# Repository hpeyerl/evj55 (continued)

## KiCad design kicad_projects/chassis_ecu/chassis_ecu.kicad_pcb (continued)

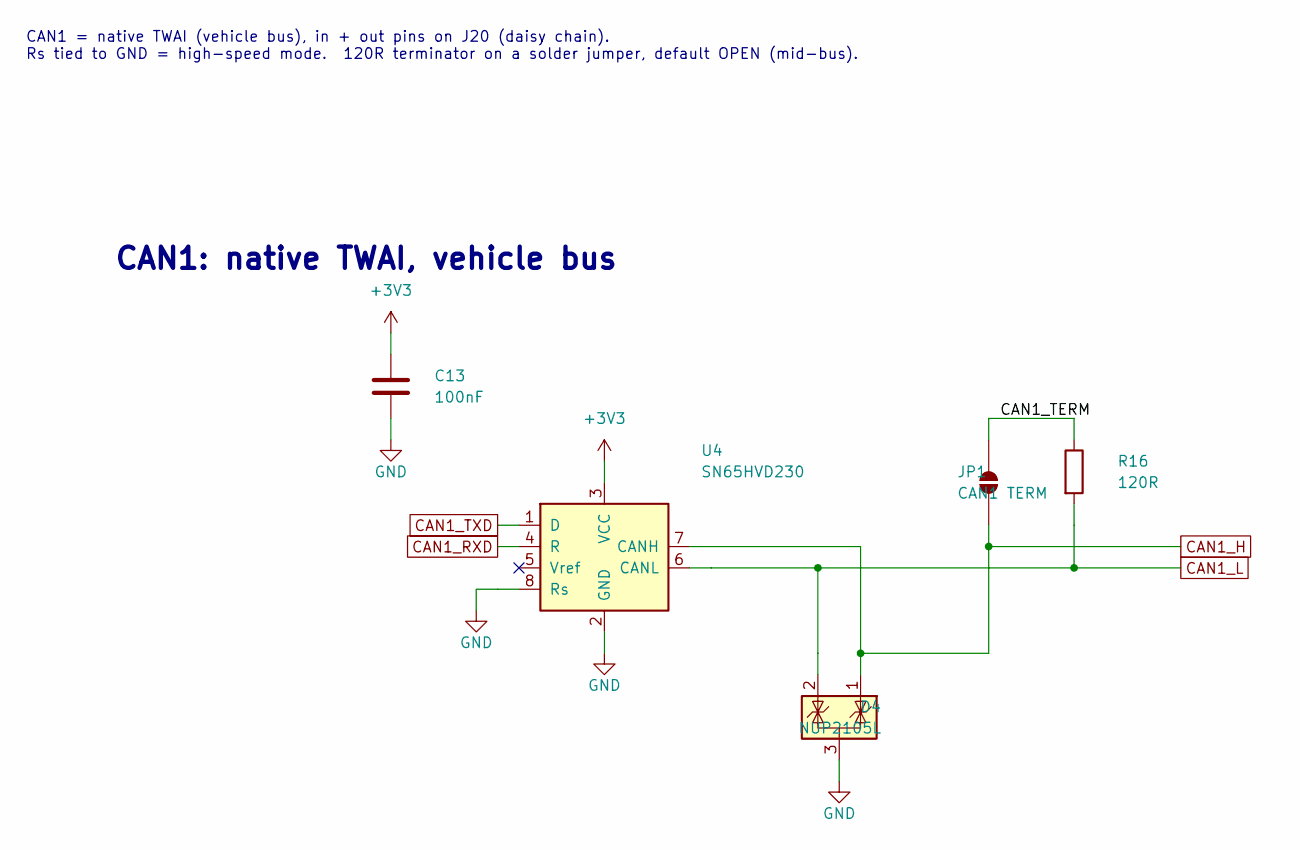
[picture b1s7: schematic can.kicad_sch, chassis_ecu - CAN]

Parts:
C13: 100nF; C_0603_1608Metric; MPN CC0603KRX7R9BB104; LCSC C14663
D4: NUP2105L; SOT-23; MPN NUP2105LT1G; LCSC C14486
JP1: CAN1 TERM; SolderJumper-2_P1.3mm_Open_RoundedPad1.0x1.5mm
R16: 120R; R_1206_3216Metric; MPN 1206W4F1200T5E; LCSC C17909
U4: SN65HVD230; SOIC-8_3.9x4.9mm_P1.27mm; MPN SN65HVD230DR; LCSC C12084

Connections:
+3V3: C13.1, U4.3 (VCC); also elsewhere on the board
/CAN/CAN1_TERM: JP1.2 (B), R16.1
CAN1_H: D4.1 (K), JP1.1 (A), U4.7 (CANH); also elsewhere on the board
CAN1_L: D4.2 (K), R16.2, U4.6 (CANL); also elsewhere on the board
CAN1_RXD: U4.4 (R); also elsewhere on the board
CAN1_TXD: U4.1 (D); also elsewhere on the board
GND: C13.2, D4.3 (A), U4.2 (GND), U4.8 (Rs); also elsewhere on the board

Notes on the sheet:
CAN1: native TWAI, vehicle bus
CAN1 = native TWAI (vehicle bus), in + out pins on J20 (daisy chain). Rs tied to GND = high-speed mode. 120R terminator on a solder jumper, default OPEN (mid-bus).

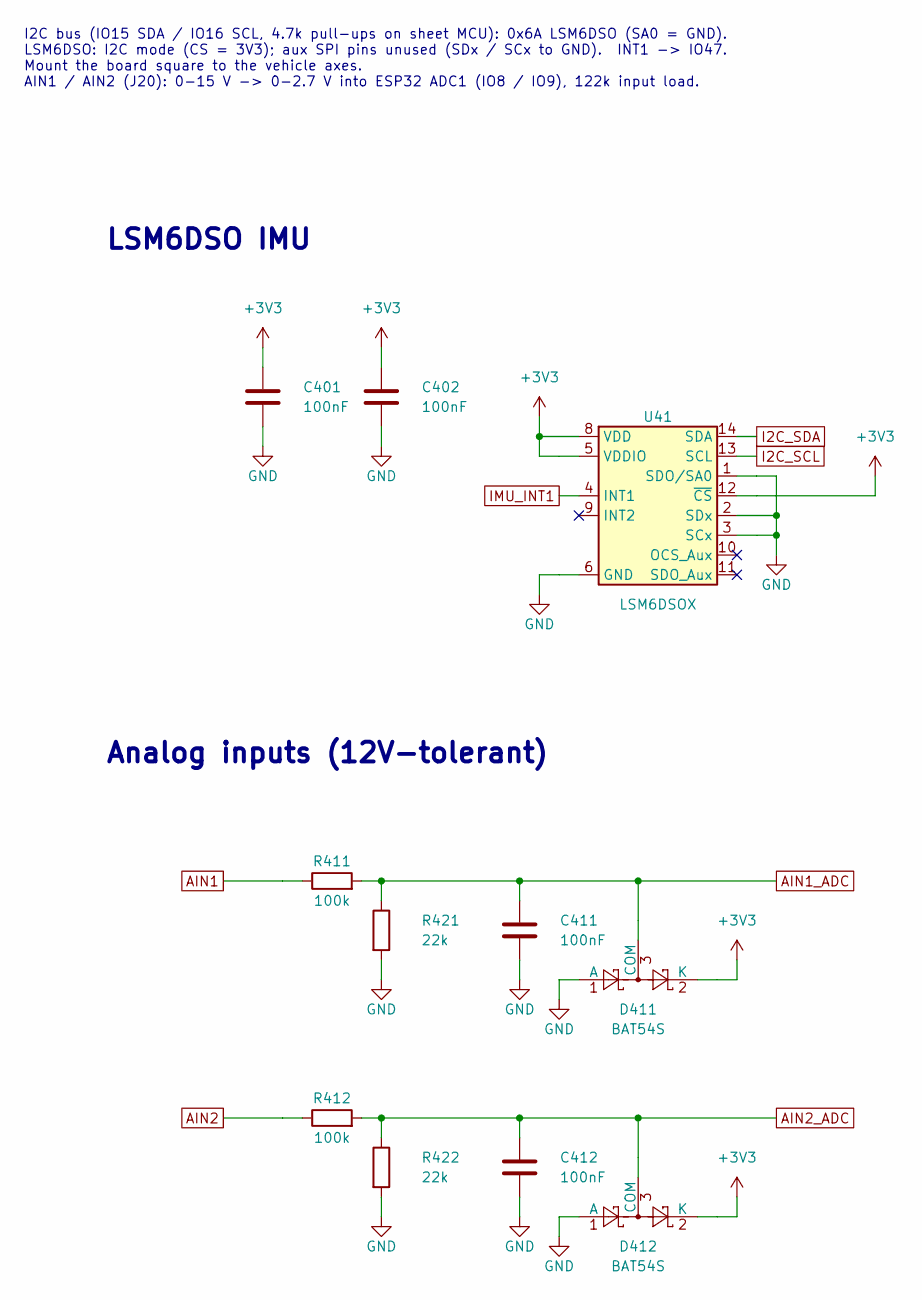
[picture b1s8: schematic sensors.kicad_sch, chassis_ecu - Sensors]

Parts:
C401, C402, C411, C412: 100nF; C_0603_1608Metric; MPN CC0603KRX7R9BB104; LCSC C14663
D411, D412: BAT54S; SOT-23; MPN BAT54S; LCSC C7420333
R411, R412: 100k; R_0603_1608Metric; MPN 0603WAF1003T5E; LCSC C25803
R421, R422: 22k; R_0603_1608Metric; MPN 0603WAF2202T5E; LCSC C31850
U41: LSM6DSOX; ST_LGA-14L_2.5x3.0mm_P0.5mm_4x3; MPN LSM6DSOXTR; LCSC C481766

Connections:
+3V3: C401.1, C402.1, D411.2 (K), D412.2 (K), U41.5 (VDDIO), U41.8 (VDD), U41.12 (~CS); also elsewhere on the board
AIN1: R411.1; also elsewhere on the board
AIN1_ADC: C411.1, D411.3 (COM), R411.2, R421.1; also elsewhere on the board
AIN2: R412.1; also elsewhere on the board
AIN2_ADC: C412.1, D412.3 (COM), R412.2, R422.1; also elsewhere on the board
GND: C401.2, C402.2, C411.2, C412.2, D411.1 (A), D412.1 (A), R421.2, R422.2, U41.1 (SDO/SA0), U41.2 (SDx), U41.3 (SCx), U41.6 (GND), U41.7 (GND); also elsewhere on the board
I2C_SCL: U41.13 (SCL); also elsewhere on the board
I2C_SDA: U41.14 (SDA); also elsewhere on the board
IMU_INT1: U41.4 (INT1); also elsewhere on the board

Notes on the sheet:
Analog inputs (12V-tolerant)
I2C bus (IO15 SDA / IO16 SCL, 4.7k pull-ups on sheet MCU): 0x6A LSM6DSO (SA0 = GND). LSM6DSO: I2C mode (CS = 3V3); aux SPI pins unused (SDx / SCx to GND). INT1 -> IO47. Mount the board square to the vehicle axes. AIN1 / AIN2 (J20): 0-15 V -> 0-2.7 V into ESP32 ADC1 (IO8 / IO9), 122k input load.
LSM6DSO IMU

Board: 4 copper layers, 124 parts (0 on the bottom side), 77 nets, no tracks yet.

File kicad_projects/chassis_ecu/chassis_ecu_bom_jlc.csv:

Comment,Designator,Footprint,LCSC
1A 63V,F1,Fuse_1206_3216Metric,C151135
SMAJ24CA,D1,D_SMA,C19077542
FDD4685,Q1,TO-252-2,C258227
10k,"R1,R9,R10,R11,R111,R112,R113,R114,R306,R307",R_0603_1608Metric,C25804
BZT52C15,D2,D_SOD-123,C19077412
47uF 63V,C1,CP_Elec_6.3x7.7,C48971005
2.2uF 100V X7R,"C2,C3",C_1210_3225Metric,C153036
LM5164DDAR,U1,,C477928
301k,R2,R_0603_1608Metric,C23026
100k,"R3,R7,R8,R411,R412",R_0603_1608Metric,C25803
27.4k,R4,R_0603_1608Metric,C843937
2.2nF 50V X7R,C4,C_0603_1608Metric,C1604
22uH 2.2A,L1,L_Changjiang_FNR6045S,C168080
124k,R5,R_0603_1608Metric,C22788
3.3nF,C5,C_0603_1608Metric,C1613
100pF,"C6,C300",C_0603_1608Metric,C14858
174k,R6,R_0603_1608Metric,C22890
22uF 10V X7R,"C7,C8,C10",C_1206_3216Metric,C12891
100nF,"C9,C11,C13,C301,C302,C401,C402,C411,C412",C_0603_1608Metric,C14663
BAT54S,"D3,D205,D411,D412",SOT-23,C7420333
ESP32-S3-WROOM-1-N4,U2,ESP32-S3-WROOM-1,C2913197
1uF,C12,C_0603_1608Metric,C15849
4.7k,"R12,R13,R245,R311",R_0603_1608Metric,C23162
TYPE-C-31-M-12,J1,USB_C_Receptacle_HRO_TYPE-C-31-M-12,C165948
5.1k,"R14,R15,R225",R_0603_1608Metric,C23186
USBLC6-2SC6,U3,SOT-23-6,C7519
SN65HVD230,U4,SOIC-8_3.9x4.9mm_P1.27mm,C12084
NUP2105L,D4,SOT-23,C14486
120R,R16,R_1206_3216Metric,C17909
4.7k,R101,R_0805_2012Metric,C17673
1N4148W,"D101,D102,D103,D104,D301",D_SOD-123,C81598
LTV-357T,"U101,U102,U103,U104",SO-4_4.4x3.6mm_P2.54mm,C119091
10nF,"C101,C102,C103,C104,C235,C304",C_0603_1608Metric,C57112
2.2k,"R102,R103,R104",R_0805_2012Metric,C17520
1k,"R164,R165,R166,R205,R215,R235,R309,R312",R_0603_1608Metric,C21190
LED green,"D121,D122,D123",LED_0603_1608Metric,C7496818
SMCJ22A,D211,D_SMC,C383717
220uF 35V,C242,CP_Elec_8x10.5,C136294
BTN8982TA,U24,,C74175
100nF 50V,C205,C_0603_1608Metric,C14663
220nF 50V,C215,C_0805_2012Metric,C5378
1nF,"C225,C303",C_0603_1608Metric,C1588
SMAJ15CA,"D300,D302",D_SMA,C19077536
2.74k 1%,R300,R_0805_2012Metric,C204367
1.3k 1%,R301,R_0805_2012Metric,C17384
CPC1117N,K1,,C150424
330R,R302,R_0603_1608Metric,C23138
200k,R303,R_0603_1608Metric,C25811
45.3k,R304,R_0603_1608Metric,C23058
57.6k,R305,R_0603_1608Metric,C23082
TLV3201AIDBV,U30,,C105188
1M,R308,R_0603_1608Metric,C22935
0R,R310,R_0805_2012Metric,C17477
LSM6DSOX,U41,,C481766
22k,"R421,R422",R_0603_1608Metric,C31850

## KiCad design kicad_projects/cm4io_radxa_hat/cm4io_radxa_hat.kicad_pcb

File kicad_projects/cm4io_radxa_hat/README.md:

A HAT for a Raspberry Pi, in this case a CM4IO carrier with a RadXA CM3 module connected to a Waveshare 12.3 TOUCHA display, and a Waveshare dual CAN hat.  

Note:  The version pictured below has the RJ45 connector backwards.  This is fixed in the current version which has not been fabbed.

This board supports:

* RevUS Parking Brake controller status LED inputs.
* Up to 4 MagRide outputs for ride control (GM coils)
* GPS input
* Dual daisy-chained CAN (RJ-45)
* Center-Diff-Lock status input.
* HF2A Transfer case Lo-Range status input.
* HF2A transfer case VSS input.
* Dimmer status input (for day/night modes)

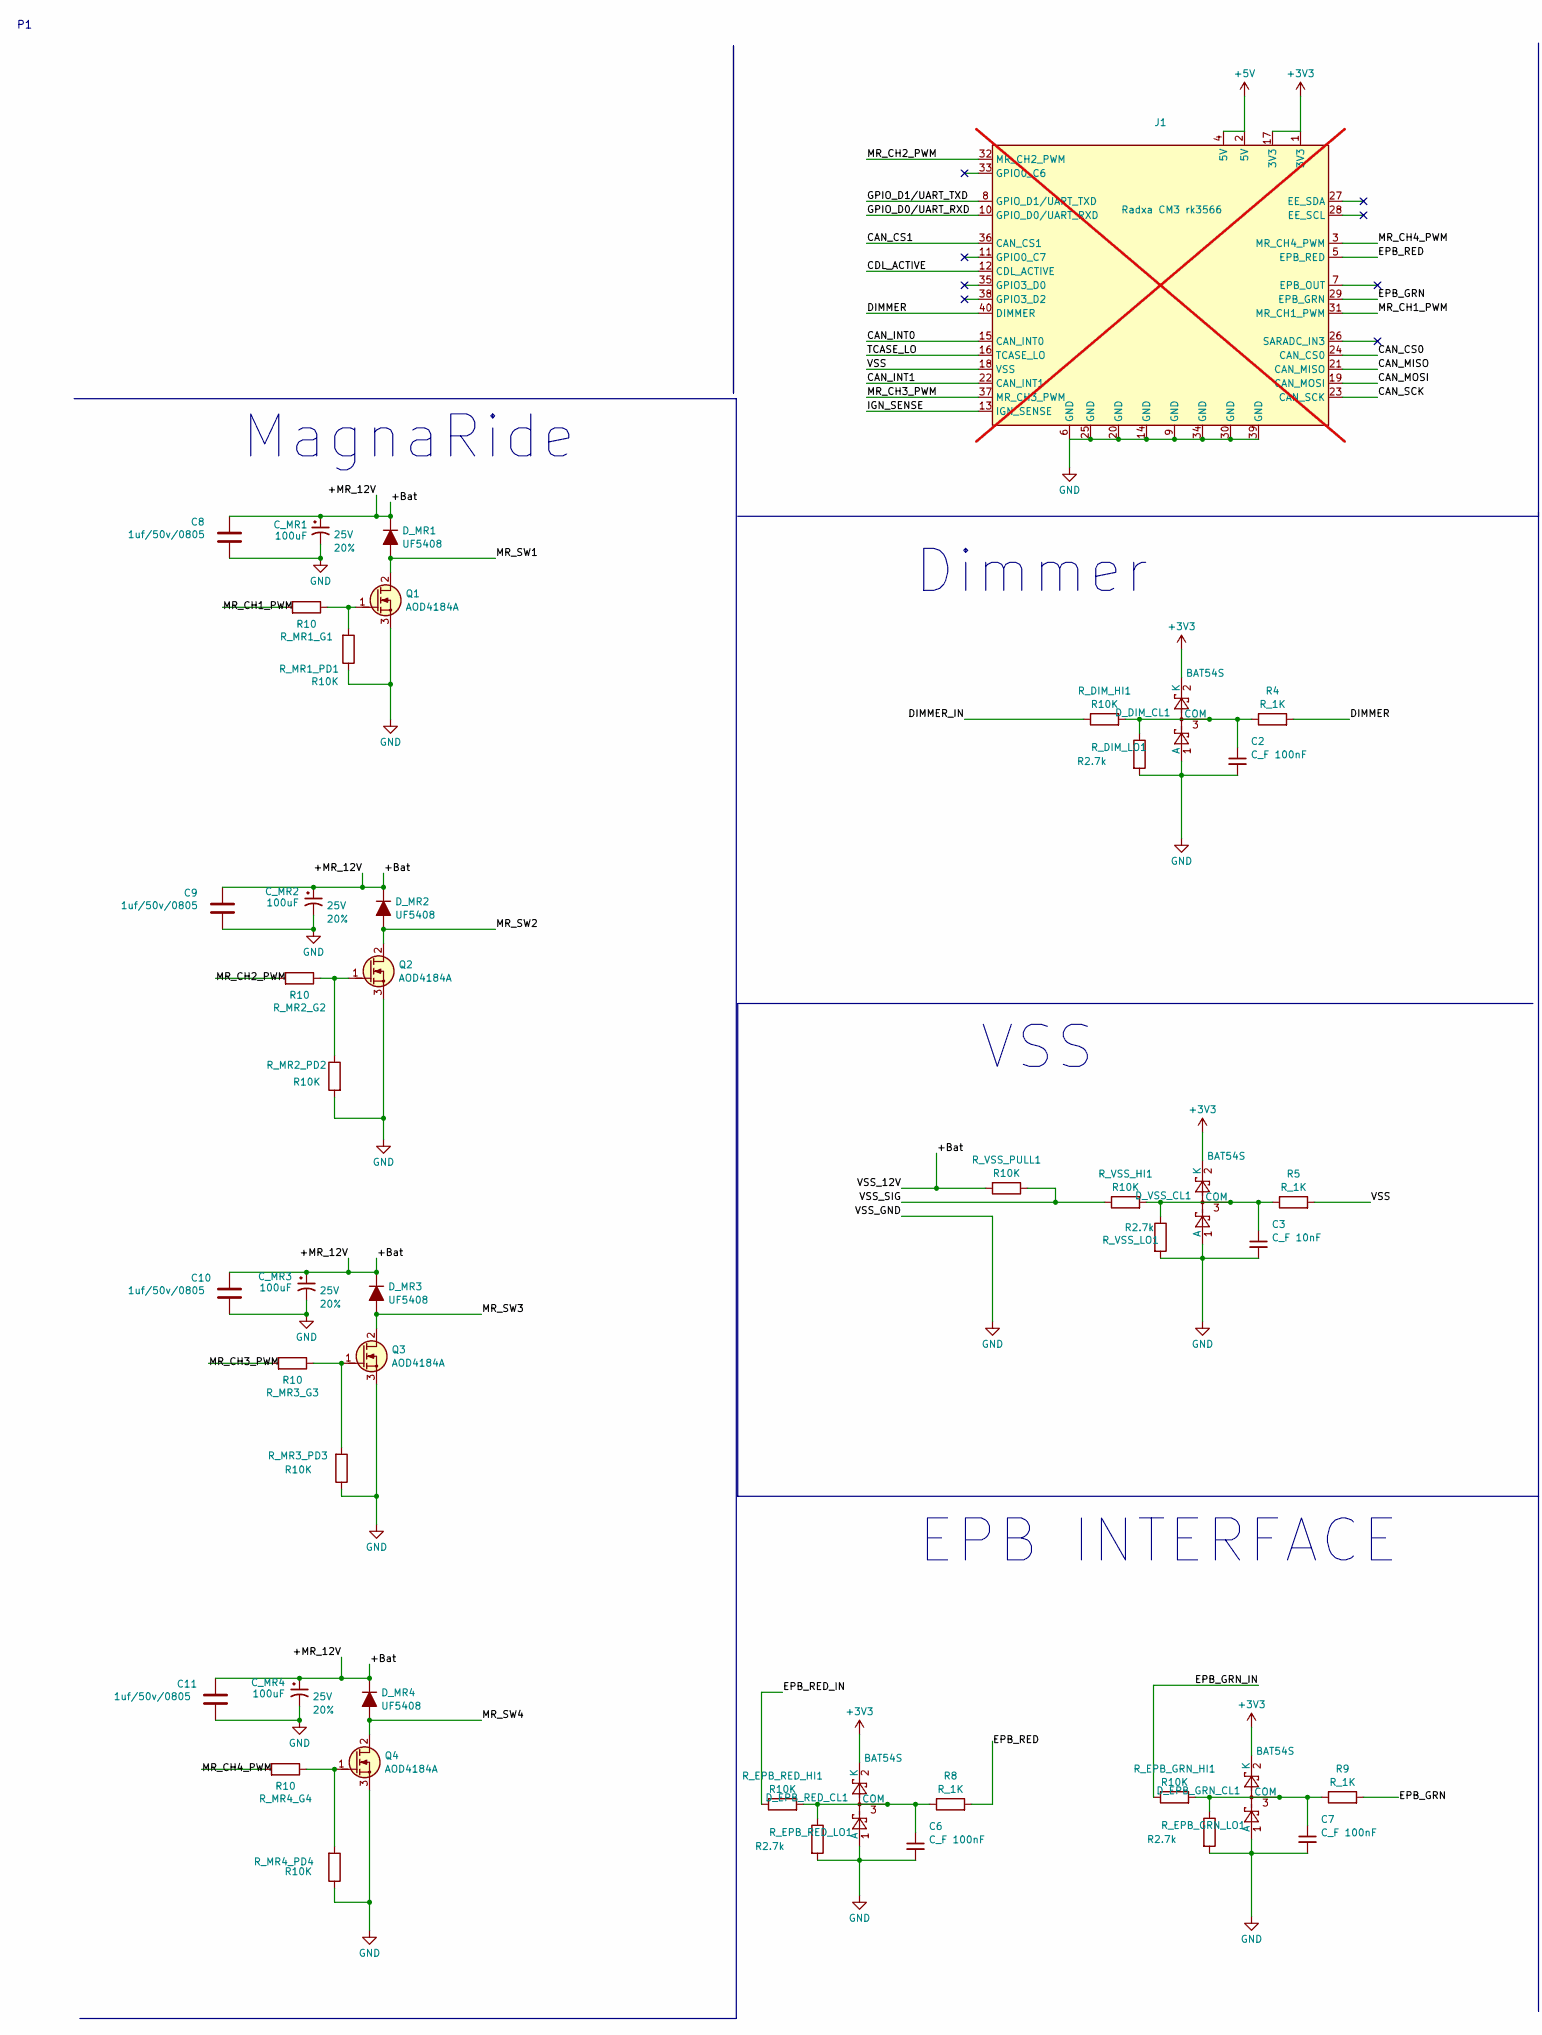
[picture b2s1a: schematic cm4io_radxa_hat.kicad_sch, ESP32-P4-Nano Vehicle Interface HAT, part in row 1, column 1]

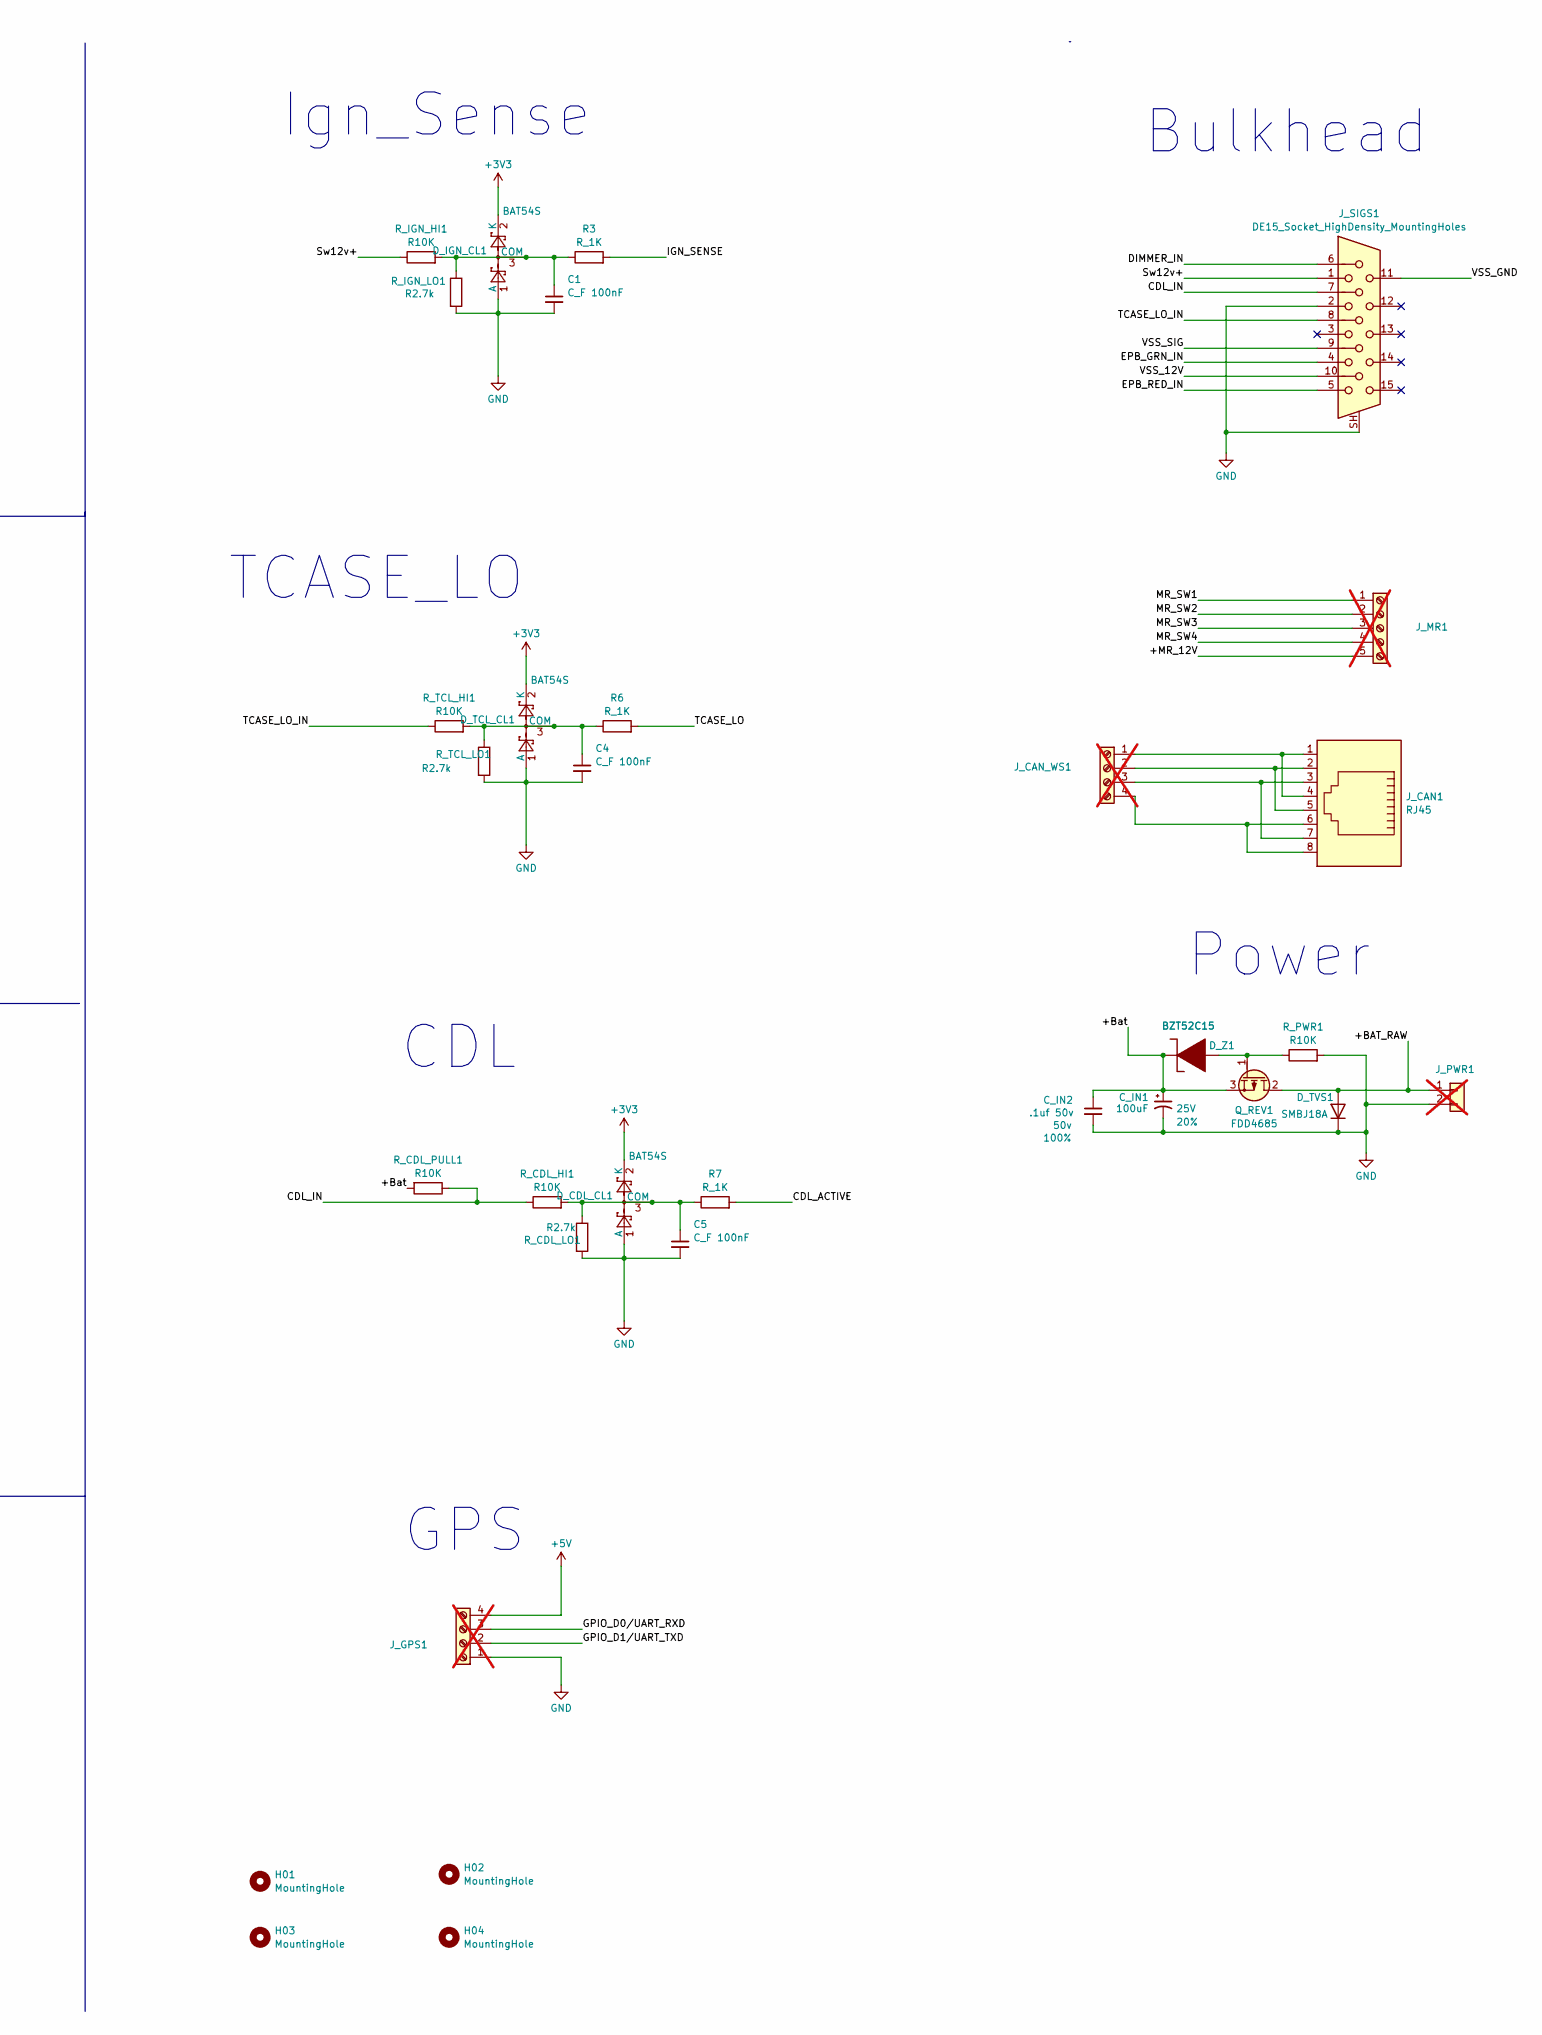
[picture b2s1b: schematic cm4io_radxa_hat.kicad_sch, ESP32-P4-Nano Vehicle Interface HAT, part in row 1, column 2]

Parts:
C1, C2, C4, C5, C6, C7: C_F 100nF; C_0402_1005Metric; Voltage 1kV; Tolerance 100%; LCSC C60474
C3: C_F 10nF; C_0402_1005Metric; Voltage 1kV; Tolerance 100%; LCSC C15195
C8, C9, C10, C11: 1uf/50v/0805; C_0805_2012Metric; LCSC C28323
C_IN1: 100uF; CP_Radial_D6.3mm_P2.50mm; Voltage 25V; Tolerance 20%; LCSC C2960218
C_IN2: .1uf 50v; C_0603_1608Metric; Voltage 50v; Tolerance 100%; LCSC C14663
C_MR1, C_MR2, C_MR3, C_MR4: 100uF; CP_Radial_D6.3mm_P2.50mm; Voltage 25V; Tolerance 20%; LCSC C2960218
D_CDL_CL1: BAT54S; SOT-23; LCSC C916425
D_DIM_CL1: BAT54S; SOT-23; LCSC C916425
D_EPB_GRN_CL1: BAT54S; SOT-23; LCSC C916425
D_EPB_RED_CL1: BAT54S; SOT-23; LCSC C916425
D_IGN_CL1: BAT54S; SOT-23; LCSC C916425
D_MR1, D_MR2, D_MR3, D_MR4: UF5408; D_DO-201AD_P5.08mm_Vertical_CathodeUp; LCSC C424502
D_TCL_CL1: BAT54S; SOT-23; LCSC C916425
D_TVS1: SMBJ18A; D_SMB_Handsoldering; LCSC C19077573
D_VSS_CL1: BAT54S; SOT-23; LCSC C916425
D_Z1: BZT52C15; D_SOD-123; LCSC C173427
H01, H02, H03, H04: MountingHole; MountingHole_2.5mm
J1: Radxa CM3 rk3566; IDC-Header_2x20_P2.54mm_Vertical; not fitted
J_CAN1: RJ45; RJ45_Amphenol_RJHSE5380; LCSC C464586
J_CAN_WS1: rr; TerminalBlock_Phoenix_PT-1,5-4-3.5-H_1x04_P3.50mm_Horizontal; not fitted
J_GPS1: Screw_Terminal_01x04; TerminalBlock_Phoenix_PT-1,5-4-3.5-H_1x04_P3.50mm_Horizontal; not fitted
J_MR1: Screw_Terminal_01x05; TerminalBlock_Phoenix_PT-1,5-5-3.5-H_1x05_P3.50mm_Horizontal; not fitted
J_PWR1: Screw_Terminal_01x02; TerminalBlock_Phoenix_PT-1,5-2-3.5-H_1x02_P3.50mm_Horizontal; not fitted
J_SIGS1: DE15_Socket_HighDensity_MountingHoles; DSUB-15-HD_Socket_Horizontal_P2.29x1.90mm_EdgePinOffset3.03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; LCSC C711364
Q1, Q2, Q3, Q4: AOD4184A; TO-252-2; LCSC C99124
Q_REV1: FDD4685; TO-252-2; LCSC C258227
R3, R4, R5, R6, R7, R8, R9: R_1K; R_0402_1005Metric; LCSC C2906864
R_CDL_HI1: R10K; R_0402_1005Metric; LCSC C25744
R_CDL_LO1: R2.7k; R_0402_1005Metric; LCSC C2909332
R_CDL_PULL1: R10K; R_0402_1005Metric; LCSC C25744
R_DIM_HI1: R10K; R_0402_1005Metric; LCSC C25744
R_DIM_LO1: R2.7k; R_0402_1005Metric; LCSC C2909332
R_EPB_GRN_HI1: R10K; R_0402_1005Metric; LCSC C25744
R_EPB_GRN_LO1: R2.7k; R_0402_1005Metric; LCSC C2909332
R_EPB_RED_HI1: R10K; R_0402_1005Metric; LCSC C25744
R_EPB_RED_LO1: R2.7k; R_0402_1005Metric; LCSC C2909332
R_IGN_HI1: R10K; R_0402_1005Metric; LCSC C25744
R_IGN_LO1: R2.7k; R_0402_1005Metric; LCSC C2909332
R_MR1_G1, R_MR2_G2, R_MR3_G3, R_MR4_G4: R10; R_0402_1005Metric; LCSC C138066
R_MR1_PD1, R_MR2_PD2, R_MR3_PD3, R_MR4_PD4: R10K; R_0402_1005Metric; LCSC C25744
R_PWR1: R10K; R_0402_1005Metric; LCSC C25744
R_TCL_HI1: R10K; R_0402_1005Metric; LCSC C25744
R_TCL_LO1: R2.7k; R_0402_1005Metric; LCSC C2909332
R_VSS_HI1: R10K; R_0402_1005Metric; LCSC C25744
R_VSS_LO1: R2.7k; R_0402_1005Metric; LCSC C2909332
R_VSS_PULL1: R10K; R_0402_1005Metric; LCSC C25744

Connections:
+3V3: D_CDL_CL1.2 (K), D_DIM_CL1.2 (K), D_EPB_GRN_CL1.2 (K), D_EPB_RED_CL1.2 (K), D_IGN_CL1.2 (K), D_TCL_CL1.2 (K), D_VSS_CL1.2 (K), J1.1 (3V3), J1.17 (3V3)
+5V: J1.2 (5V), J1.4 (5V), J_GPS1.4
/+BAT_RAW: D_TVS1.2 (A), J_PWR1.1, Q_REV1.2 (D)
/+Bat: C8.1, C9.1, C10.1, C11.1, C_IN1.1, C_IN2.1, C_MR1.1, C_MR2.1, C_MR3.1, C_MR4.1, D_MR1.1 (K), D_MR2.1 (K), D_MR3.1 (K), D_MR4.1 (K), D_Z1.1 (K-), J_MR1.5, J_SIGS1.10, Q_REV1.3 (S), R_CDL_PULL1.2, R_VSS_PULL1.2
/CAN_CS0: J1.24 (CAN_CS0)
/CAN_CS1: J1.36 (CAN_CS1)
/CAN_INT0: J1.15 (CAN_INT0)
/CAN_INT1: J1.22 (CAN_INT1)
/CAN_MISO: J1.21 (CAN_MISO)
/CAN_MOSI: J1.19 (CAN_MOSI)
/CAN_SCK: J1.23 (CAN_SCK)
/CDL_ACTIVE: J1.12 (CDL_ACTIVE), R7.2
/CDL_IN: J_SIGS1.7, R_CDL_HI1.1, R_CDL_PULL1.1
/DIMMER: J1.40 (DIMMER), R4.2
/DIMMER_IN: J_SIGS1.6, R_DIM_HI1.1
/EPB_GRN: J1.29 (EPB_GRN), R9.2
/EPB_GRN_IN: J_SIGS1.4, R_EPB_GRN_HI1.1
/EPB_RED: J1.5 (EPB_RED), R8.2
/EPB_RED_IN: J_SIGS1.5, R_EPB_RED_HI1.1
/GPIO_D0/UART_RXD: J1.10 (GPIO_D0/UART_RXD), J_GPS1.3
/GPIO_D1/UART_TXD: J1.8 (GPIO_D1/UART_TXD), J_GPS1.2
/IGN_SENSE: J1.13 (IGN_SENSE), R3.2
/MR_CH1_PWM: J1.31 (MR_CH1_PWM), R_MR1_G1.1
/MR_CH2_PWM: J1.32 (MR_CH2_PWM), R_MR2_G2.1
/MR_CH3_PWM: J1.37 (MR_CH3_PWM), R_MR3_G3.1
/MR_CH4_PWM: J1.3 (MR_CH4_PWM), R_MR4_G4.1
/MR_SW1: D_MR1.2 (A), J_MR1.1, Q1.2 (D)
/MR_SW2: D_MR2.2 (A), J_MR1.2, Q2.2 (D)
/MR_SW3: D_MR3.2 (A), J_MR1.3, Q3.2 (D)
/MR_SW4: D_MR4.2 (A), J_MR1.4, Q4.2 (D)
/Sw12v+: J_SIGS1.1, R_IGN_HI1.1
/TCASE_LO: J1.16 (TCASE_LO), R6.2
/TCASE_LO_IN: J_SIGS1.8, R_TCL_HI1.1
/VSS: J1.18 (VSS), R5.2
/VSS_SIG: J_SIGS1.9, R_VSS_HI1.1, R_VSS_PULL1.1
GND: C1.2, C2.2, C3.2, C4.2, C5.2, C6.2, C7.2, C8.2, C9.2, C10.2, C11.2, C_IN1.2, C_IN2.2, C_MR1.2, C_MR2.2, C_MR3.2, C_MR4.2, D_CDL_CL1.1 (A), D_DIM_CL1.1 (A), D_EPB_GRN_CL1.1 (A), D_EPB_RED_CL1.1 (A), D_IGN_CL1.1 (A), D_TCL_CL1.1 (A), D_TVS1.1 (K), D_VSS_CL1.1 (A), J1.6 (GND), J1.9 (GND), J1.14 (GND), J1.20 (GND), J1.25 (GND), J1.30 (GND), J1.34 (GND), J1.39 (GND), J_GPS1.1, J_PWR1.2, J_SIGS1.2, J_SIGS1.11, J_SIGS1.SH, Q1.3 (S), Q2.3 (S), Q3.3 (S), Q4.3 (S), R_CDL_LO1.2, R_DIM_LO1.2, R_EPB_GRN_LO1.2, R_EPB_RED_LO1.2, R_IGN_LO1.2, R_MR1_PD1.2, R_MR2_PD2.1, R_MR3_PD3.2, R_MR4_PD4.2, R_PWR1.1, R_TCL_LO1.2, R_VSS_LO1.2
unnamed: C5.1, D_CDL_CL1.3 (COM), R7.1, R_CDL_HI1.2, R_CDL_LO1.1
unnamed: C2.1, D_DIM_CL1.3 (COM), R4.1, R_DIM_HI1.2, R_DIM_LO1.1
unnamed: C7.1, D_EPB_GRN_CL1.3 (COM), R9.1, R_EPB_GRN_HI1.2, R_EPB_GRN_LO1.1
unnamed: C6.1, D_EPB_RED_CL1.3 (COM), R8.1, R_EPB_RED_HI1.2, R_EPB_RED_LO1.1
unnamed: C1.1, D_IGN_CL1.3 (COM), R3.1, R_IGN_HI1.2, R_IGN_LO1.1
unnamed: C4.1, D_TCL_CL1.3 (COM), R6.1, R_TCL_HI1.2, R_TCL_LO1.1
unnamed: C3.1, D_VSS_CL1.3 (COM), R5.1, R_VSS_HI1.2, R_VSS_LO1.1
unnamed: D_Z1.2 (A+), Q_REV1.1 (G), R_PWR1.2
unnamed: J_CAN1.1, J_CAN1.4, J_CAN_WS1.1
unnamed: J_CAN1.2, J_CAN1.5, J_CAN_WS1.2
unnamed: J_CAN1.3, J_CAN1.7, J_CAN_WS1.3
unnamed: J_CAN1.6, J_CAN1.8, J_CAN_WS1.4
unnamed: Q1.1 (G), R_MR1_G1.2, R_MR1_PD1.1
unnamed: Q2.1 (G), R_MR2_G2.2, R_MR2_PD2.2
unnamed: Q3.1 (G), R_MR3_G3.2, R_MR3_PD3.1
unnamed: Q4.1 (G), R_MR4_G4.2, R_MR4_PD4.1

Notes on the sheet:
EPB INTERFACE
TCASE_LO
VSS
MagnaRide
GPS
CDL
Power
Bulkhead
Dimmer
Ign_Sense

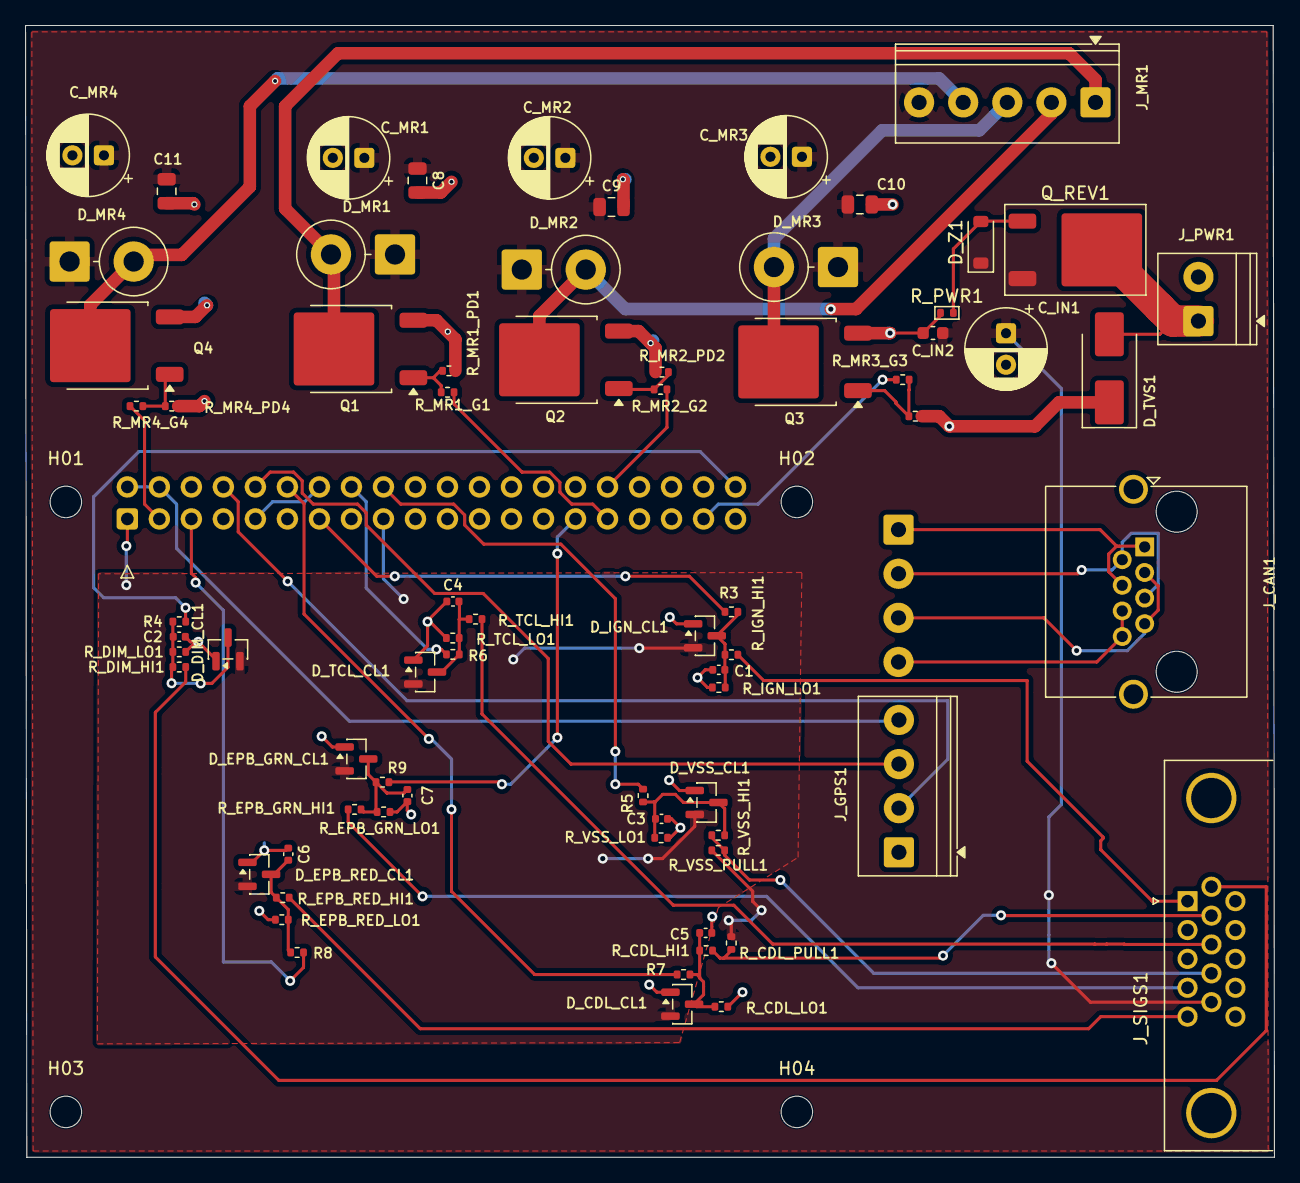
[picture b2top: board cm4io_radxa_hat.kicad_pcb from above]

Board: 2 copper layers, 99.1 x 89.8 mm, 78 parts (1 on the bottom side), 45 nets.

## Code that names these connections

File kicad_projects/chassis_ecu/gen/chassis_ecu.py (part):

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           'runs from 12V, so bench programming needs the 12V supply.\n'
           'ADC1 (IO1-10) for analog; ADC2 is unusable with WiFi.\n'
           'ADC1: IO1 CP_LVL, IO2 PP_SENSE, IO4/5/10 ANA1-3 (J10), IO6 PAWL_IS, IO7 VSENSE_12V, IO8/9 AIN1/2.\n'
           'Opto inputs IO35-38 (active-low), PAWL_INH IO39, status LEDs IO17 / IO18, J10 GPIO IO11 / IO12.\n'
           'CAN1 TXD / RXD on IO40 / IO21: IO17 / IO18 glitch at power-up (datasheet table 2-2).  CAN1_RS IO13.\n'
           'ADC1 effective range 0-2.9 V (12 dB attenuation).\n'
           'BOOT / RESET = solder-jumper pads (short with tweezers); USB auto-reset covers normal flashing.\n'
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        'GND': 'GND', '3V3': '+3V3', 'EN': 'ESP_EN', 'IO0': 'ESP_BOOT',
        'IO1': 'CP_LVL', 'IO2': 'PP_SENSE', 'IO4': 'ANA1', 'IO5': 'ANA2', 'IO6': 'PAWL_IS',
        'IO7': 'VSENSE_12V', 'IO8': 'AIN1_ADC', 'IO9': 'AIN2_ADC', 'IO10': 'ANA3', 'IO47': 'IMU_INT1',
        'IO11': 'EXP_GPIO1', 'IO12': 'EXP_GPIO2', 'IO21': 'CAN1_RXD', 'IO13': 'CAN1_RS',
        'IO15': 'I2C_SDA', 'IO16': 'I2C_SCL',
        'IO35': 'OPTO_IN1', 'IO36': 'OPTO_IN2', 'IO37': 'OPTO_IN3', 'IO38': 'OPTO_IN4',
        'IO39': 'PAWL_INH', 'IO40': 'CAN1_TXD',
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    s = b.sheet('IO', 'io.kicad_sch')
    s.note('Opto inputs -> native GPIO IO35-38, ACTIVE-LOW (collector pulled up to 3V3).\n'
           'Opto inputs: 12V -> 2.2k (IN1 P_SENSE 4.7k: light tap on a shared sense line) -> LTV-357T.\n'
           'J10 (DNP) expansion: I2C, ANA1-3 (raw ESP32 ADC1, 0-2.9 V), 2 GPIO.',
           20, 15)
    s.paper = 'A3'
    s.head('Opto inputs (12V active)', 30.48, 33.02)
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    s.head('Expansion header (DNP)', 30.48, 167.64)
    s.add('J10', 'Connector_Generic:Conn_01x10', 'EXP', {
        '1': 'GND', '2': '+3V3', '3': 'I2C_SDA', '4': 'I2C_SCL', '5': 'ANA1', '6': 'ANA2',
        '7': 'ANA3', '8': 'EXP_GPIO1', '9': 'EXP_GPIO2', '10': 'GND'},
        'Connector_PinHeader_2.54mm:PinHeader_1x10_P2.54mm_Vertical', dnp=True, at=(101.6, 205.74), rot=270)


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    s = b.sheet('J1772', 'j1772.kicad_sch')
    s.note('Car-side pilot.  CP -> diode -> 2.74k to GND (state B, always) ; 1.3k via K1 to GND (state C).\n'
           'K1 = CPC1117N, form-B (CLOSED when unpowered): a dead board presents state C, so the EVSE delivers\n'
           'AC and Pin-B wakes the truck.  CP_S2_OPEN high = LED on = K1 open = state B (pause / stop).\n'
           'CP read: 200k / 45.3k to 3V3 / 57.6k to GND maps CP -12..+12 V to 0.3..3.0 V (CP 0 V = 1.65 V),\n'
           'load on CP >= 200k.  TLV3201 vs 1.65 V, 1M hysteresis (~0.7 V at CP) -> CP_DUTY (MCPWM capture).\n'
           'CP_SENSE -> 1k/1nF -> CP_LVL -> ESP32 ADC1 IO1: +12 / +9 / +6 V = 3.0 / 2.66 / 2.33 V (state A / B / C);\n'
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
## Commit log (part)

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2025-05-06 Play with Wireviz
2025-05-06 Start documenting
2025-05-07 Workaround lack of include feature in yaml by using cpp
2025-05-07 latest output file
2025-05-07 fix pin names on BMW throttle pedal
2025-05-09 Need to build the harnesses as modules. It will be too unwieldy to have one single harness schematic
2025-05-09 pin changes from @robertwa
2025-05-09 colorize the inverter/resolver cables
2025-05-09 Start documenting our HF1A tcase wiring
2025-05-13 clean up include dependencies
2025-05-13 add some connector images. Wire up the oil pump connector
2025-05-15 Need a README to add some words to this
2025-05-15 Switch to Honda Fit pedal
2025-05-15 start incorporating notes from old FJ55LV wiring diagrams
2025-05-15 image for honda_fit_pedal_connector from openinverter wiki
2025-05-16 pinlabels were reversed between mg1/mg2
2025-05-16 fix some errors after review. Document the shields on the resolver cables
2025-05-16 move zombie stuff to its own repo and create submodule for it here
2025-09-14 HF1A tcase is actually an HF2A
2025-12-15 update submodule
2025-12-25 remove some connector images that are in the zombie repo
2025-12-25 play with wireviz-web
2025-12-26 update per 93 FZJ80 FSM schematic p5
2026-01-03 Add wiring for ibooster GEN1 from Honda CRV 2019
2026-01-03 Housekeeping
2026-01-26 Images for fuses, milround and transmission control relay
2026-01-26 don't ignore png's
2026-01-30 Create a README?
2026-01-30 L110F stuff
2026-01-30 Rename
2026-01-30 HF2A-L110F adapter. V4 and not yet cut
2026-01-30 Oil pump adapter. V2. This was the version milled at jlccnc
2026-01-30 Describe each file a bit
2026-01-30 emphasize file names
2026-02-02 Parts that differ from stock
2026-02-02 another couple parts
2026-02-02 Add a tantalizing image
2026-02-03 switch to better color
2026-02-04 before and after
2026-02-04 updates to README
2026-02-06 Remove O-ring bosses because they prevent sealing of the cavity next to the ports causing leaks.
2026-04-15 Move Wireviz stuff to its own dir. Import current wiring plan from SpliceCad
2026-04-16 A git action to hopefully render my Splice-Cad wiring harness
2026-04-16 chore: update rendered wiring outputs [skip ci]
2026-04-16 more changes
2026-04-18 Update wiring/EVJ-55_plan.json via splice
2026-04-18 Update splice.yml via splice
2026-04-20 Update render workflow via splice
2026-04-20 chore: update rendered outputs [skip ci]
2026-05-19 System Diagram WIP
2026-06-07 updated system diagram and document scope creep under consideration
2026-06-07 a mechanical system diagram
2026-06-07 cleanup system diagrams a bit
